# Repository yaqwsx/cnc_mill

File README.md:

# My CNC mill

This repository contains everything related to the
build of my CNC mill. The mill is driven by LinuxCNC.

## Structure

- `arduino_sketches` - I am not a fan of Arduino,
however it is great tool for simple prototypes.
All source codes for prototypes is here.

- `config` - LinuxCNC configuration and HAL files for
the mill

- `hal_modules` - LinuxCNC HAL modules for my custom
hardware

- `hw_modules` - PCBs & firmware for custom hardware

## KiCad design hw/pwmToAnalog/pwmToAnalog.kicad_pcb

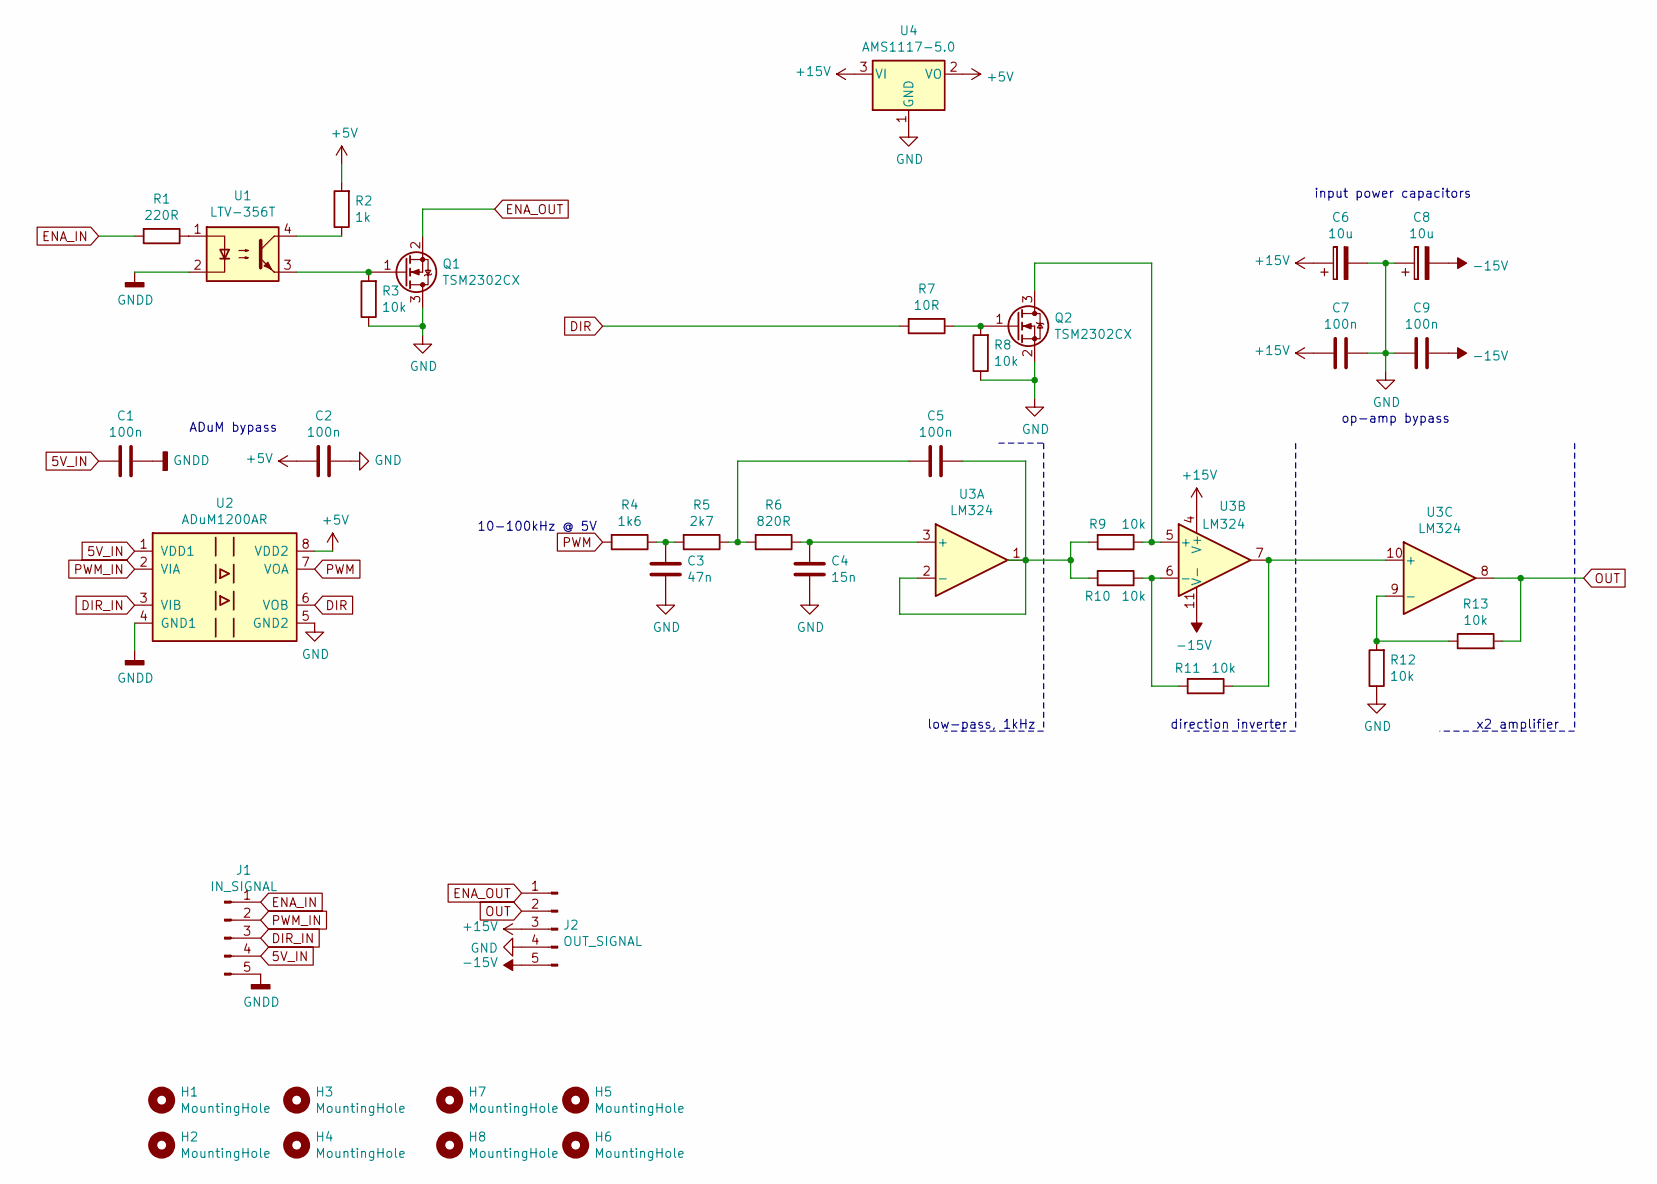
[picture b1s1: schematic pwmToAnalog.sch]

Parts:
C1, C2, C5, C7, C9: 100n; C_0603_1608Metric_Pad1.05x0.95mm_HandSolder
C3: 47n; C_0603_1608Metric_Pad1.05x0.95mm_HandSolder
C4: 15n; C_0603_1608Metric_Pad1.05x0.95mm_HandSolder
C6, C8: 10u; CP_Elec_8x5.4
H1, H2, H3, H4, H5, H6, H7, H8: MountingHole; MountingHole_3.2mm_M3
J1: IN_SIGNAL; TerminalBlock_Phoenix_MKDS-1,5-5_1x05_P5.00mm_Horizontal
J2: OUT_SIGNAL; TerminalBlock_Phoenix_MKDS-1,5-5_1x05_P5.00mm_Horizontal
Q1, Q2: TSM2302CX; SOT-23
R1: 220R; R_0603_1608Metric_Pad1.05x0.95mm_HandSolder
R2: 1k; R_0603_1608Metric_Pad1.05x0.95mm_HandSolder
R3, R8, R9, R10, R11, R12, R13: 10k; R_0603_1608Metric_Pad1.05x0.95mm_HandSolder
R4: 1k6; R_0603_1608Metric_Pad1.05x0.95mm_HandSolder
R5: 2k7; R_0603_1608Metric_Pad1.05x0.95mm_HandSolder
R6: 820R; R_0603_1608Metric_Pad1.05x0.95mm_HandSolder
R7: 10R; R_0603_1608Metric_Pad1.05x0.95mm_HandSolder
U1: LTV-356T; SO-4_4.4x3.6mm_P2.54mm
U2: ADuM1200AR; SOIC-8_3.9x4.9mm_P1.27mm
U3: LM324; SOIC-14_3.9x8.7mm_P1.27mm
U4: AMS1117-5.0; SOT-223-3_TabPin2

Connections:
5V_IN: C1.2, J1.4, U2.1 (VDD1)
+5V: C2.2, R2.2, U2.8 (VDD2), U4.2 (VO)
+15V: C6.1, C7.1, J2.3, U3.4 (V+), U4.3 (VI)
-15V: C8.2, C9.2, J2.5, U3.11 (V-)
DIR: R7.2, U2.6 (VOB)
DIR_IN: J1.3, U2.3 (VIB)
ENA_IN: J1.1, R1.2
ENA_OUT: J2.1, Q1.2 (S)
GND: C2.1, C3.2, C4.2, C6.2, C7.2, C8.1, C9.1, J2.4, Q1.3 (D), Q2.2 (S), R3.1, R8.1, R12.1, U2.5 (GND2), U4.1 (GND)
GNDD: C1.1, J1.5, U1.2, U2.4 (GND1)
unnamed: C3.1, R4.1, R5.2
unnamed: C4.1, R6.1, U3.3 (+)
unnamed: C5.1, R9.2, R10.2, U3.1, U3.2 (-)
unnamed: C5.2, R5.1, R6.2
unnamed: Q1.1 (G), R3.2, U1.3
unnamed: Q2.1 (G), R7.1, R8.2
unnamed: Q2.3 (D), R9.1, U3.5 (+)
unnamed: R1.1, U1.1
unnamed: R2.1, U1.4
unnamed: R10.1, R11.2, U3.6 (-)
unnamed: R11.1, U3.7, U3.10 (+)
unnamed: R12.2, R13.1, U3.9 (-)
OUT: J2.2, R13.2, U3.8
PWM: R4.2, U2.7 (VOA)
PWM_IN: J1.2, U2.2 (VIA)

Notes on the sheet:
low-pass, 1kHz
direction inverter
x2 amplifier
ADuM bypass
op-amp bypass
input power capacitors
10-100kHz @ 5V

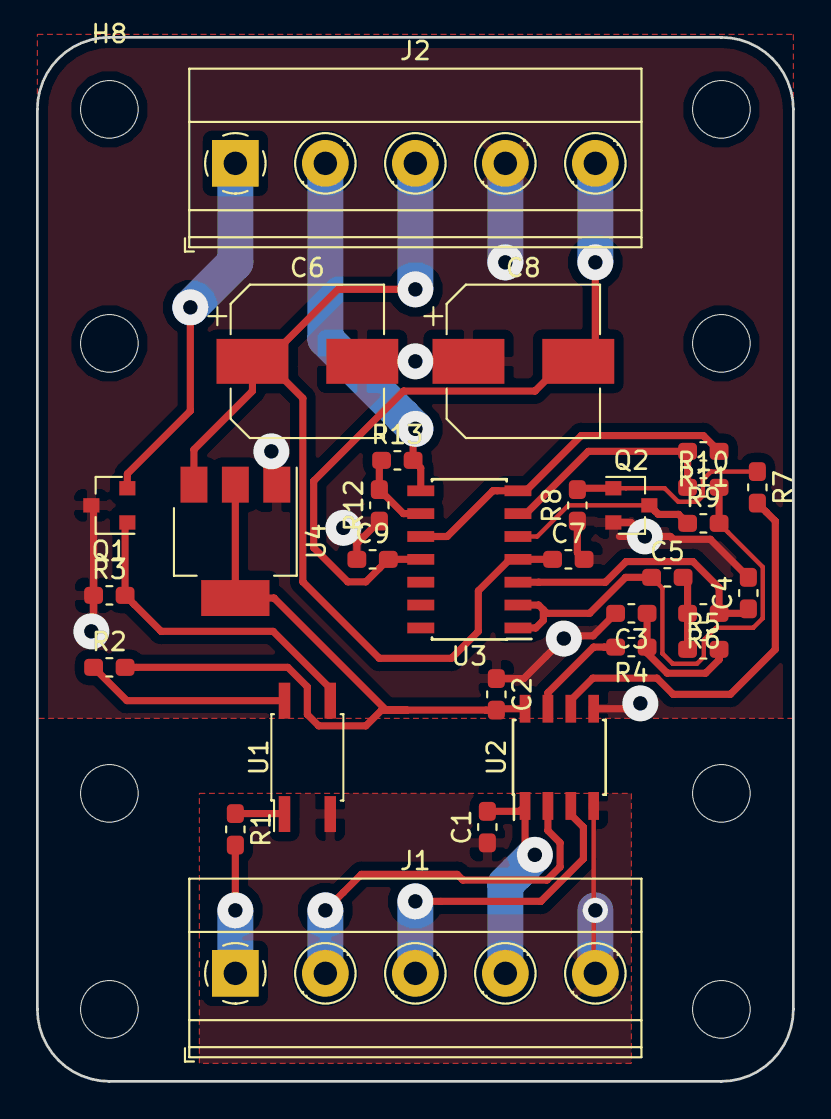
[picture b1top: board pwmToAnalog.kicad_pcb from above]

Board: 2 copper layers, 42.0 x 58.0 mm, 38 parts (0 on the bottom side), 25 nets.

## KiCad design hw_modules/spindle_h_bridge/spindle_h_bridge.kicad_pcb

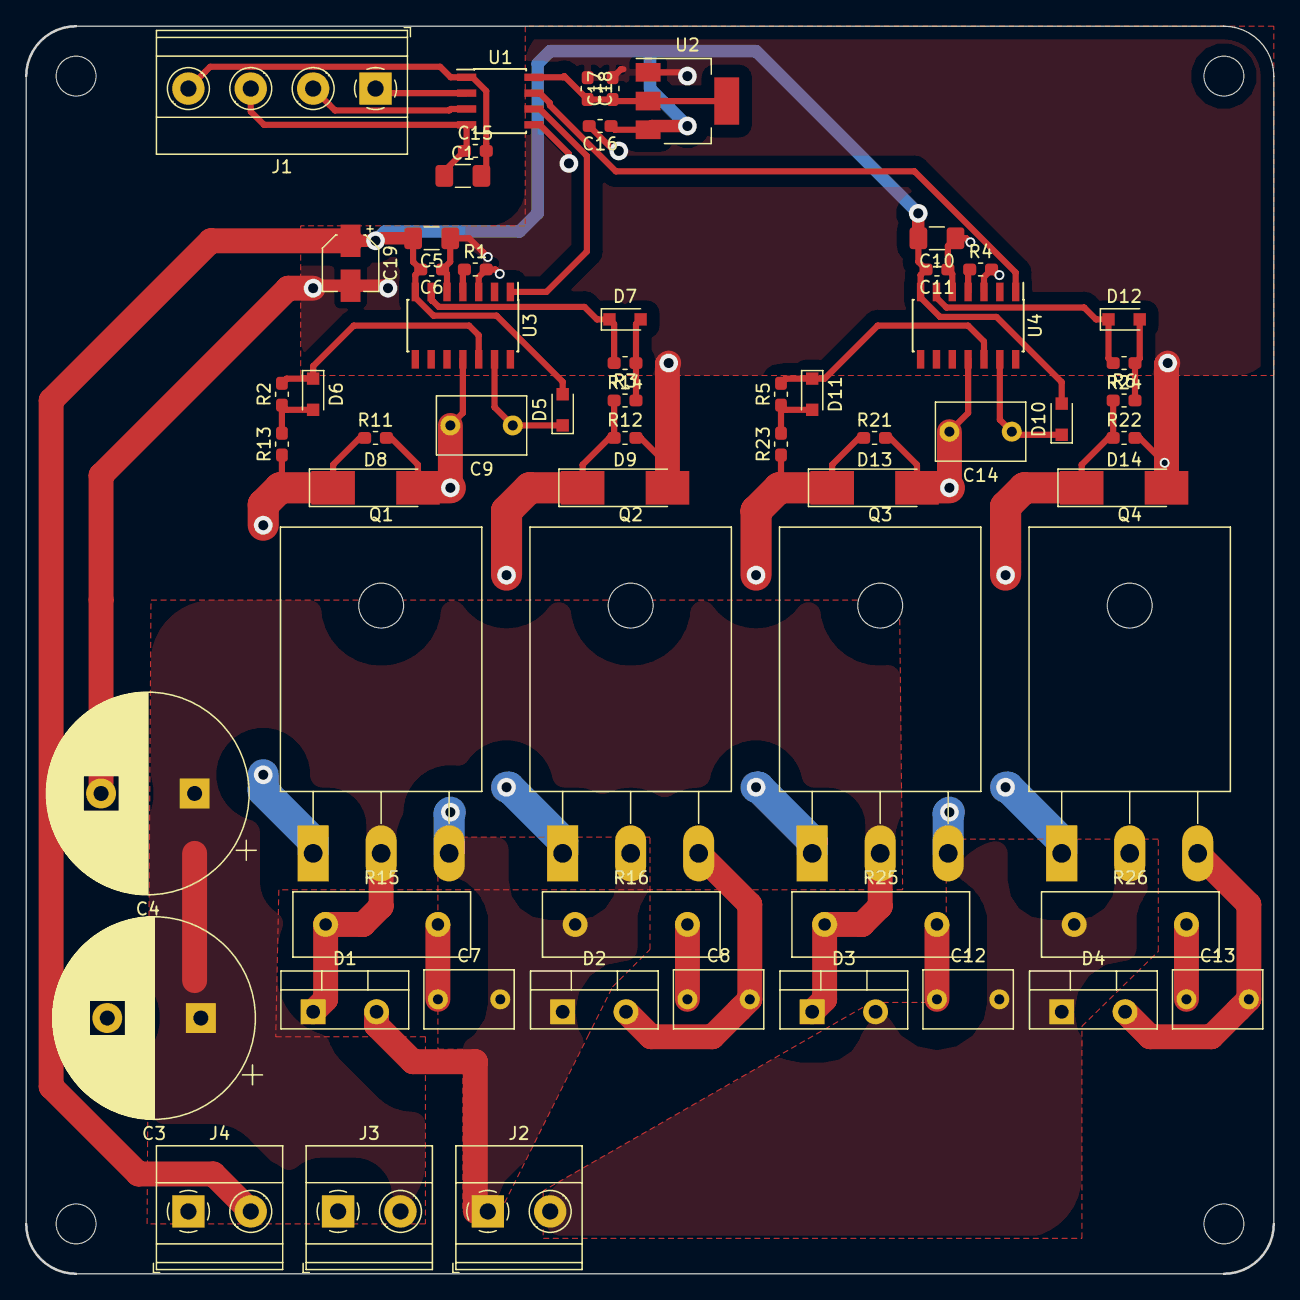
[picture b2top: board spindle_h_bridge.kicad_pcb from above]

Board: 4 copper layers, 100.0 x 100.0 mm, 66 parts (0 on the bottom side), 32 nets.

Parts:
C1: 2u2; C_1206_3216Metric_Pad1.42x1.75mm_HandSolder
C3: 220u 400V; CP_Radial_D16.0mm_P7.50mm
C4: 10u 400V; CP_Radial_D16.0mm_P7.50mm
C5, C10: 1u; C_1206_3216Metric_Pad1.42x1.75mm_HandSolder
C6, C11, C15, C16, C18: 100n; C_0603_1608Metric_Pad1.05x0.95mm_HandSolder
C7, C8, C9, C12, C13, C14: 100n 400V; C_Rect_L7.0mm_W4.5mm_P5.00mm
C17: 10u; C_0603_1608Metric_Pad1.05x0.95mm_HandSolder
C19: 10u; CP_Elec_4x4.5
D1, D2, D3, D4: STTH15R06; TO-220-2_Vertical
D5, D6, D7, D10, D11, D12: BAT42; D_SOD-323_HandSoldering
D8, D9, D13, D14: 18V; D_MELF_Handsoldering
H1, H2, H3, H4: MountingHole; MountingHole_3.2mm_M3
J1: SIGNAL; TerminalBlock_Phoenix_MKDS-1,5-4_1x04_P5.00mm_Horizontal
J2: MOTOR; TerminalBlock_Phoenix_MKDS-1,5-2_1x02_P5.00mm_Horizontal
J3, J4: POWER; TerminalBlock_Phoenix_MKDS-1,5-2_1x02_P5.00mm_Horizontal
Q1, Q2, Q3, Q4: IRG4PH40U; TO-247-3_Horizontal_TabDown
R1, R4: 25k; R_0603_1608Metric_Pad1.05x0.95mm_HandSolder
R2, R3, R5, R6: 10R; R_0603_1608Metric_Pad1.05x0.95mm_HandSolder
R11, R12, R21, R22: 10k; R_0603_1608Metric_Pad1.05x0.95mm_HandSolder
R13, R14, R23, R24: 4R7; R_0603_1608Metric_Pad1.05x0.95mm_HandSolder
R15, R16, R25, R26: 0R5; R_Box_L14.0mm_W5.0mm_P9.00mm
U1: ADuM1200AR; SOIC-8_3.9x4.9mm_P1.27mm
U2: LM1117-5.0; SOT-223
U3, U4: FAN7393A; SOIC-14_3.9x8.7mm_P1.27mm

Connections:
+5V: C1.2, C15.2, J1.4, U1.1
+15V: C5.2, C6.2, C10.2, C11.2, C16.1, C19.1, D5.2, D10.2, J4.2, U2.3, U3.7, U4.7
/left-half-bridge/OUT: C7.2, C9.2, D1.2, D2.1, D8.2, J2.1, Q1.3, Q2.2, R11.2, R16.1, U3.11
/left-half-bridge/PWM: U1.6, U3.1
/right-half-bridge/OUT: C12.2, C14.2, D3.2, D4.1, D13.2, J2.2, Q3.3, Q4.2, R21.2, R26.1, U4.11
/right-half-bridge/PWM: U1.7, U4.1
A: J1.1, U1.2
B: J1.2, U1.3
GND: C3.2, C4.2, C5.1, C6.1, C8.2, C10.1, C11.1, C13.2, C16.2, C17.2, C18.1, C19.2, D2.2, D4.2, D9.2, D14.2, J3.1, J4.1, Q2.3, Q4.3, R1.2, R4.2, R12.2, R22.2, U1.5, U2.1, U3.3, U3.5, U4.3, U4.5
GNDD: C1.1, C15.1, J1.3, U1.4
unnamed: C7.1, R15.2
unnamed: C8.1, R16.2
unnamed: C9.1, D5.1, U3.13
unnamed: C12.1, R25.2
unnamed: C13.1, R26.2
unnamed: C14.1, D10.1, U4.13
unnamed: C17.1, C18.2, U1.8, U2.2, U2.4
unnamed: D6.1, R2.2, U3.12
unnamed: D6.2, R2.1, R13.2
unnamed: D7.1, R3.2, U3.6
unnamed: D7.2, R3.1, R14.2
unnamed: D8.1, Q1.1, R11.1, R13.1
unnamed: D9.1, Q2.1, R12.1, R14.1
unnamed: D11.1, R5.2, U4.12
unnamed: D11.2, R5.1, R23.2
unnamed: D12.1, R6.2, U4.6
unnamed: D12.2, R6.1, R24.2
unnamed: D13.1, Q3.1, R21.1, R23.1
unnamed: D14.1, Q4.1, R22.1, R24.1
unnamed: R1.1, U3.4
unnamed: R4.1, U4.4
VCC: C3.1, C4.1, D1.1, D3.1, J3.2, Q1.2, Q3.2, R15.1, R25.1

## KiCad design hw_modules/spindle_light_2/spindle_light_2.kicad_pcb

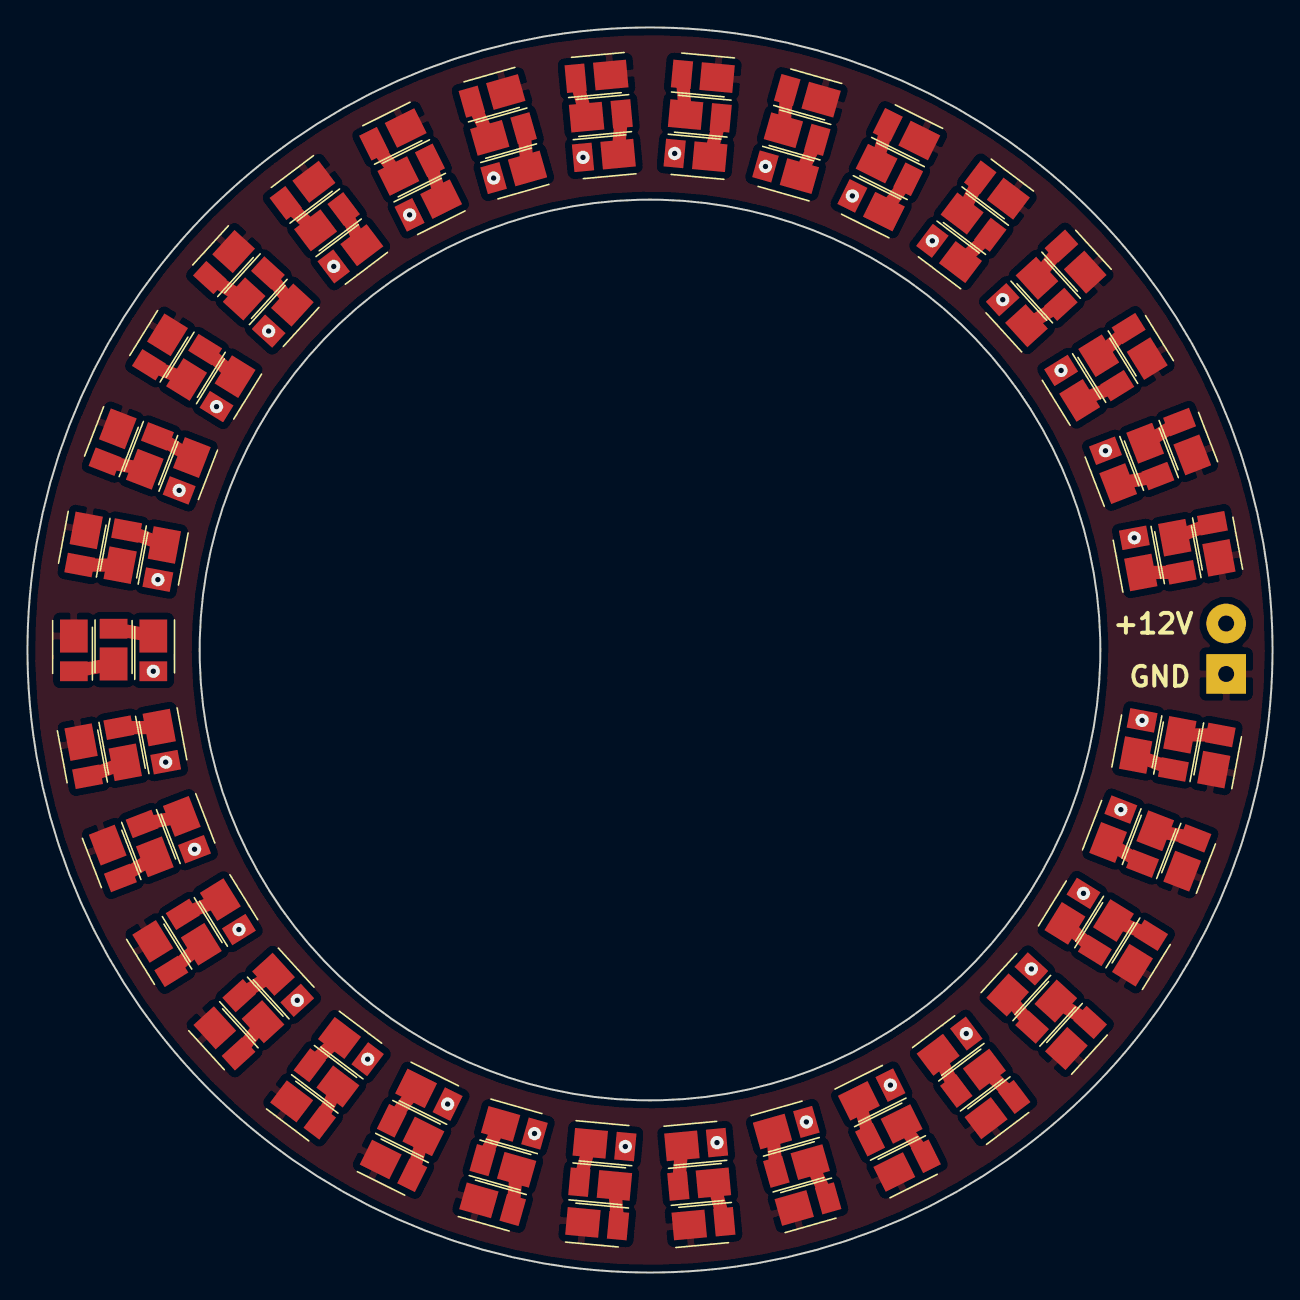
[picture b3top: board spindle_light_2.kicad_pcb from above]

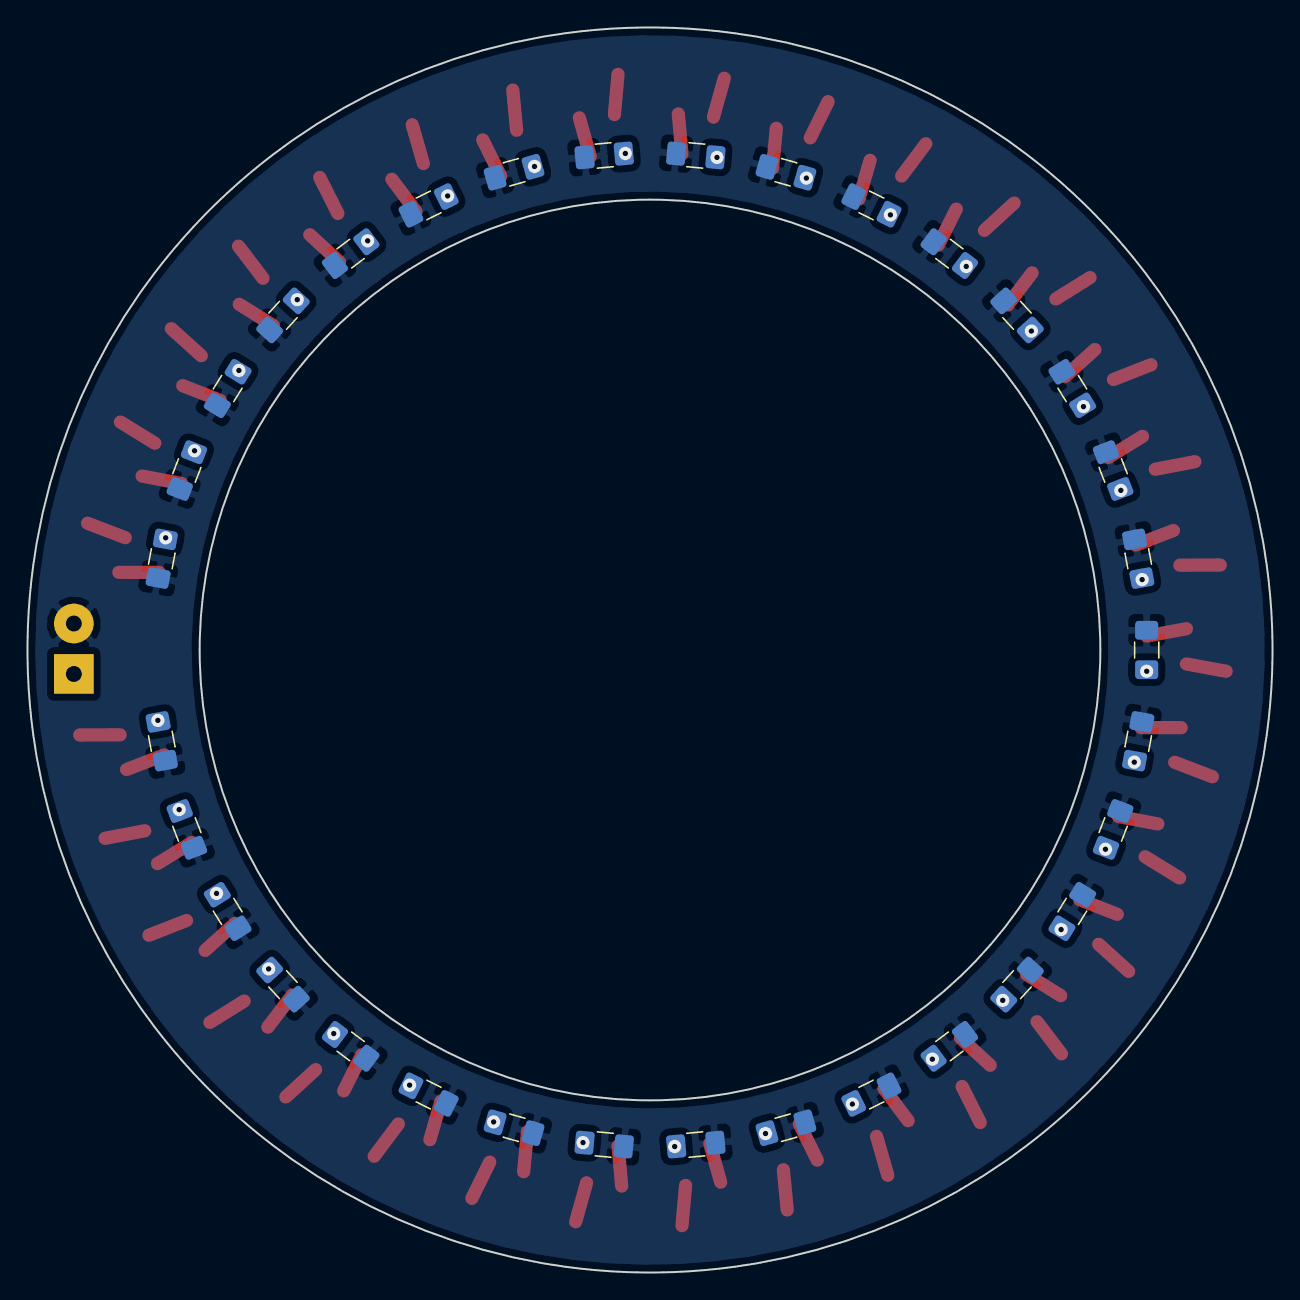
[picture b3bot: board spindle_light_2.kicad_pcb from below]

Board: 2 copper layers, 94.0 x 94.0 mm, 133 parts (33 on the bottom side), 101 nets.

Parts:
D1, D2, D3, D4, D5, D6, D7, D8, D9, D10, D11, D12, D13, D14, D15, D16, D17, D18, D19, D20, D21, D22, D23, D24, D25, D26, D27, D28, D29, D30, D31, D32, D33, D34, D35, D36, D37, D38, D39, D40, D41, D42, D43, D44, D45, D46, D47, D48, D49, D50, D51, D52, D53, D54, D55, D56, D57, D58, D59, D60, D61, D62, D63, D64, D65, D66, D67, D68, D69, D70, D71, D72, D73, D74, D75, D76, D77, D78, D79, D80, D81, D82, D83, D84, D85, D86, D87, D88, D89, D90, D91, D92, D93, D94, D95, D96, D97, D98, D99: LED; LED_PLCC_2835_Handsoldering_Centered
J1: Power; SolderWirePad_1x02_P3.81mm_Drill1.2mm
R1, R2, R3, R4, R5, R6, R7, R8, R9, R10, R11, R12, R13, R14, R15, R16, R17, R18, R19, R20, R21, R22, R23, R24, R25, R26, R27, R28, R29, R30, R31, R32, R33: 47R; R_1206_3216Metric_Pad1.42x1.75mm_HandSolder

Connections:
+12V: J1.2, R1.1, R2.1, R3.1, R4.1, R5.1, R6.1, R7.1, R8.1, R9.1, R10.1, R11.1, R12.1, R13.1, R14.1, R15.1, R16.1, R17.1, R18.1, R19.1, R20.1, R21.1, R22.1, R23.1, R24.1, R25.1, R26.1, R27.1, R28.1, R29.1, R30.1, R31.1, R32.1, R33.1
GND: D3.1, D6.1, D9.1, D12.1, D15.1, D18.1, D21.1, D24.1, D27.1, D30.1, D33.1, D36.1, D39.1, D42.1, D45.1, D48.1, D51.1, D54.1, D57.1, D60.1, D63.1, D66.1, D69.1, D72.1, D75.1, D78.1, D81.1, D84.1, D87.1, D90.1, D93.1, D96.1, D99.1, J1.1
unnamed: D1.1, D2.2
unnamed: D1.2, R1.2
unnamed: D2.1, D3.2
unnamed: D4.1, D5.2
unnamed: D4.2, R2.2
unnamed: D5.1, D6.2
unnamed: D7.1, D8.2
unnamed: D7.2, R3.2
unnamed: D8.1, D9.2
unnamed: D10.1, D11.2
unnamed: D10.2, R4.2
unnamed: D11.1, D12.2
unnamed: D13.1, D14.2
unnamed: D13.2, R5.2
unnamed: D14.1, D15.2
unnamed: D16.1, D17.2
unnamed: D16.2, R6.2
unnamed: D17.1, D18.2
unnamed: D19.1, D20.2
unnamed: D19.2, R7.2
unnamed: D20.1, D21.2
unnamed: D22.1, D23.2
unnamed: D22.2, R8.2
unnamed: D23.1, D24.2
unnamed: D25.1, D26.2
unnamed: D25.2, R9.2
unnamed: D26.1, D27.2
unnamed: D28.1, D29.2
unnamed: D28.2, R10.2
unnamed: D29.1, D30.2
unnamed: D31.1, D32.2
unnamed: D31.2, R11.2
unnamed: D32.1, D33.2
unnamed: D34.1, D35.2
unnamed: D34.2, R12.2
unnamed: D35.1, D36.2
unnamed: D37.1, D38.2
unnamed: D37.2, R13.2
unnamed: D38.1, D39.2
unnamed: D40.1, D41.2
unnamed: D40.2, R14.2
unnamed: D41.1, D42.2
unnamed: D43.1, D44.2
unnamed: D43.2, R15.2
unnamed: D44.1, D45.2
unnamed: D46.1, D47.2
unnamed: D46.2, R16.2
unnamed: D47.1, D48.2
unnamed: D49.1, D50.2
unnamed: D49.2, R17.2
unnamed: D50.1, D51.2
unnamed: D52.1, D53.2
unnamed: D52.2, R18.2
unnamed: D53.1, D54.2
unnamed: D55.1, D56.2
unnamed: D55.2, R19.2
unnamed: D56.1, D57.2
unnamed: D58.1, D59.2
unnamed: D58.2, R20.2
unnamed: D59.1, D60.2
unnamed: D61.1, D62.2
unnamed: D61.2, R21.2
unnamed: D62.1, D63.2
unnamed: D64.1, D65.2
unnamed: D64.2, R22.2
unnamed: D65.1, D66.2
unnamed: D67.1, D68.2
unnamed: D67.2, R23.2
unnamed: D68.1, D69.2
unnamed: D70.1, D71.2
unnamed: D70.2, R24.2
unnamed: D71.1, D72.2
unnamed: D73.1, D74.2
unnamed: D73.2, R25.2
unnamed: D74.1, D75.2
unnamed: D76.1, D77.2
unnamed: D76.2, R26.2
unnamed: D77.1, D78.2
unnamed: D79.1, D80.2
unnamed: D79.2, R27.2
unnamed: D80.1, D81.2
unnamed: D82.1, D83.2
unnamed: D82.2, R28.2
unnamed: D83.1, D84.2
unnamed: D85.1, D86.2
unnamed: D85.2, R29.2
unnamed: D86.1, D87.2
unnamed: D88.1, D89.2
unnamed: D88.2, R30.2
unnamed: D89.1, D90.2
unnamed: D91.1, D92.2
unnamed: D91.2, R31.2
unnamed: D92.1, D93.2
unnamed: D94.1, D95.2
unnamed: D94.2, R32.2
unnamed: D95.1, D96.2
unnamed: D97.1, D98.2
unnamed: D97.2, R33.2
unnamed: D98.1, D99.2

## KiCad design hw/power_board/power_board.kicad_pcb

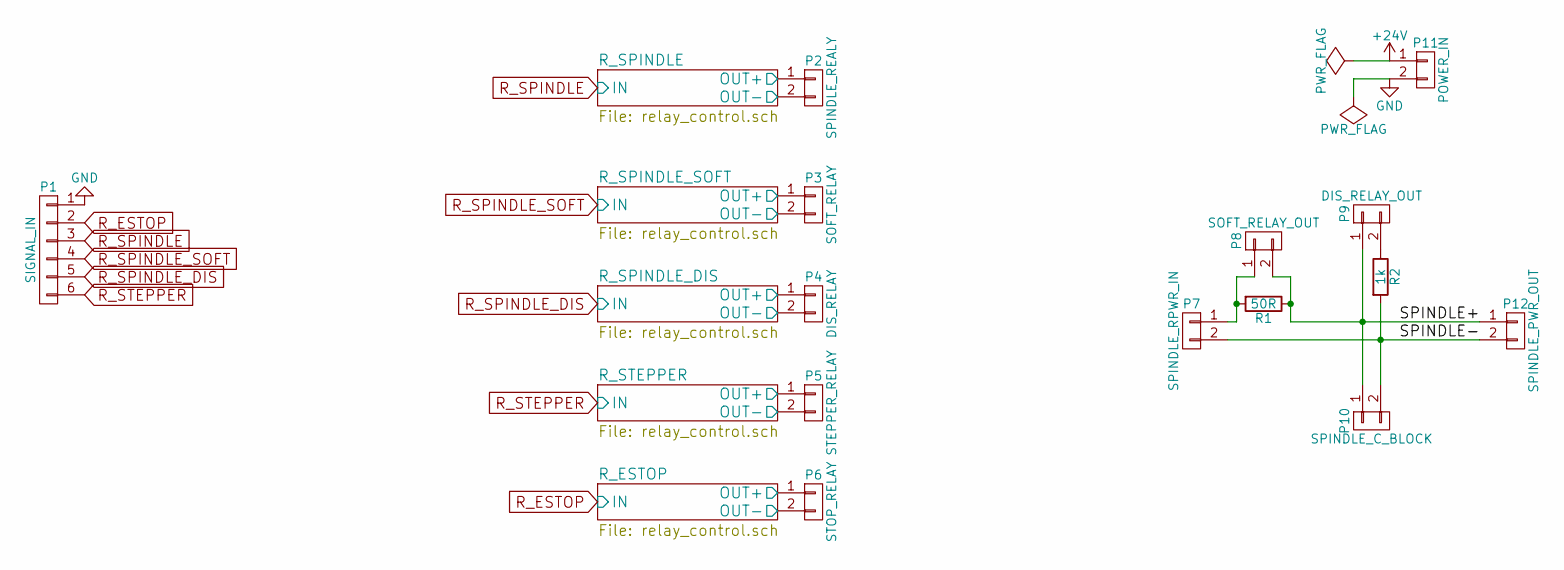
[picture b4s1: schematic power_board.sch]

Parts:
P1: SIGNAL_IN; TerminalBlock_Pheonix_MKDS1.5-6pol
P2: SPINDLE_REALY; TerminalBlock_Pheonix_MKDS1.5-2pol
P3: SOFT_RELAY; TerminalBlock_Pheonix_MKDS1.5-2pol
P4: DIS_RELAY; TerminalBlock_Pheonix_MKDS1.5-2pol
P5: STEPPER_RELAY; TerminalBlock_Pheonix_MKDS1.5-2pol
P6: STOP_RELAY; TerminalBlock_Pheonix_MKDS1.5-2pol
P7: SPINDLE_RPWR_IN; TerminalBlock_Pheonix_MKDS1.5-2pol
P8: SOFT_RELAY_OUT; TerminalBlock_Pheonix_MKDS1.5-2pol
P9: DIS_RELAY_OUT; TerminalBlock_Pheonix_MKDS1.5-2pol
P10: SPINDLE_C_BLOCK; TerminalBlock_Pheonix_MKDS1.5-2pol
P11: POWER_IN; TerminalBlock_Pheonix_MKDS1.5-2pol
P12: SPINDLE_PWR_OUT; TerminalBlock_Pheonix_MKDS1.5-2pol
R1: 50R; Resistor_Horizontal_RM30mm
R2: 1k; Resistor_Horizontal_RM30mm

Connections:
+24V: P2.1, P3.1, P4.1, P5.1, P6.1, P11.1; also elsewhere on the board
/R_ESTOP/OUT-: P6.2; also elsewhere on the board
/R_SPINDLE/OUT-: P2.2; also elsewhere on the board
/R_SPINDLE_DIS/OUT-: P4.2; also elsewhere on the board
/R_SPINDLE_SOFT/OUT-: P3.2; also elsewhere on the board
/R_STEPPER/OUT-: P5.2; also elsewhere on the board
/SPINDLE+: P8.2, P9.1, P10.1, P12.1, R1.1
/SPINDLE-: P7.2, P10.2, P12.2, R2.2
GND: P1.1, P11.2; also elsewhere on the board
unnamed: P7.1, P8.1, R1.2
unnamed: P9.2, R2.1
R_ESTOP: P1.2; also elsewhere on the board
R_SPINDLE: P1.3; also elsewhere on the board
R_SPINDLE_DIS: P1.5; also elsewhere on the board
R_SPINDLE_SOFT: P1.4; also elsewhere on the board
R_STEPPER: P1.6; also elsewhere on the board

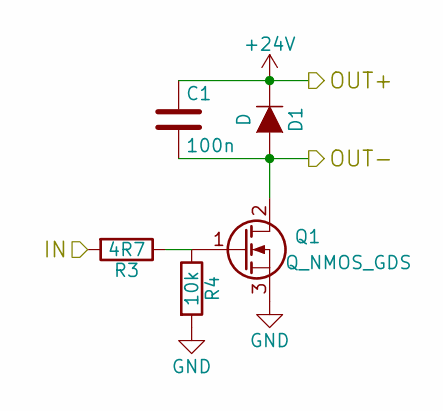
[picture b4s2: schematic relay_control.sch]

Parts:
C1: 100n; C_0603
D1: D; SOD-523
Q1: Q_NMOS_GDS; SOT-223
R3: 4R7; R_0603
R4: 10k; R_0603

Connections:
+24V: C1.1, D1.1 (K); also elsewhere on the board
/R_SPINDLE/OUT-: C1.2, D1.2 (A), Q1.2 (D); also elsewhere on the board
GND: Q1.3 (S), R4.2; also elsewhere on the board
unnamed: Q1.1 (G), R3.1, R4.1
R_SPINDLE: R3.2; also elsewhere on the board

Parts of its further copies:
C2, C3, C4, C5: 100n; C_0603
D2, D3, D4, D5: D; SOD-523
Q2, Q3, Q4, Q5: Q_NMOS_GDS; SOT-223
R5, R7, R9, R11: 4R7; R_0603
R6, R8, R10, R12: 10k; R_0603

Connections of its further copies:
+24V: C2.1, C3.1, C4.1, C5.1, D2.1 (K), D3.1 (K), D4.1 (K), D5.1 (K); also elsewhere on the board
/R_ESTOP/OUT-: C5.2, D5.2 (A), Q5.2 (D); also elsewhere on the board
/R_SPINDLE_DIS/OUT-: C3.2, D3.2 (A), Q3.2 (D); also elsewhere on the board
/R_SPINDLE_SOFT/OUT-: C2.2, D2.2 (A), Q2.2 (D); also elsewhere on the board
/R_STEPPER/OUT-: C4.2, D4.2 (A), Q4.2 (D); also elsewhere on the board
GND: Q2.3 (S), Q3.3 (S), Q4.3 (S), Q5.3 (S), R6.2, R8.2, R10.2, R12.2; also elsewhere on the board
unnamed: Q2.1 (G), R5.1, R6.1
unnamed: Q3.1 (G), R7.1, R8.1
unnamed: Q4.1 (G), R9.1, R10.1
unnamed: Q5.1 (G), R11.1, R12.1
R_ESTOP: R11.2; also elsewhere on the board
R_SPINDLE_DIS: R7.2; also elsewhere on the board
R_SPINDLE_SOFT: R5.2; also elsewhere on the board
R_STEPPER: R9.2; also elsewhere on the board

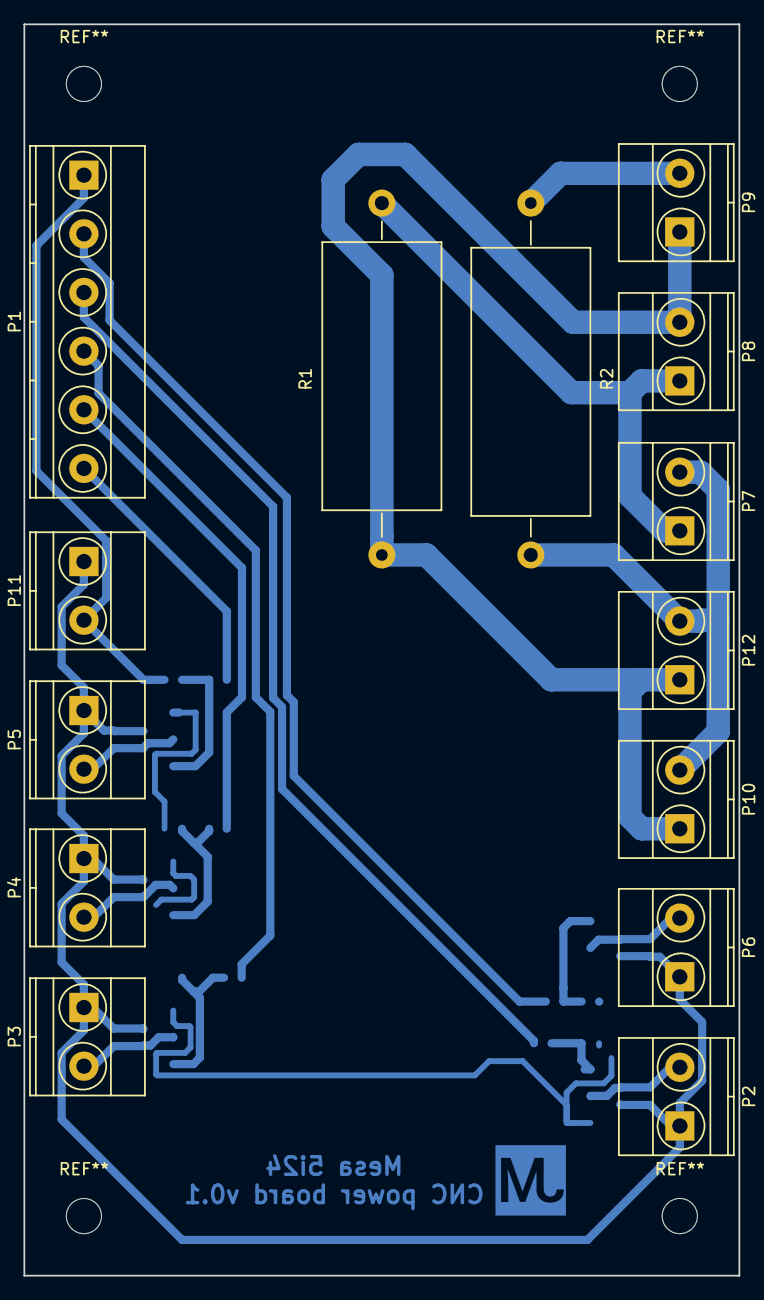
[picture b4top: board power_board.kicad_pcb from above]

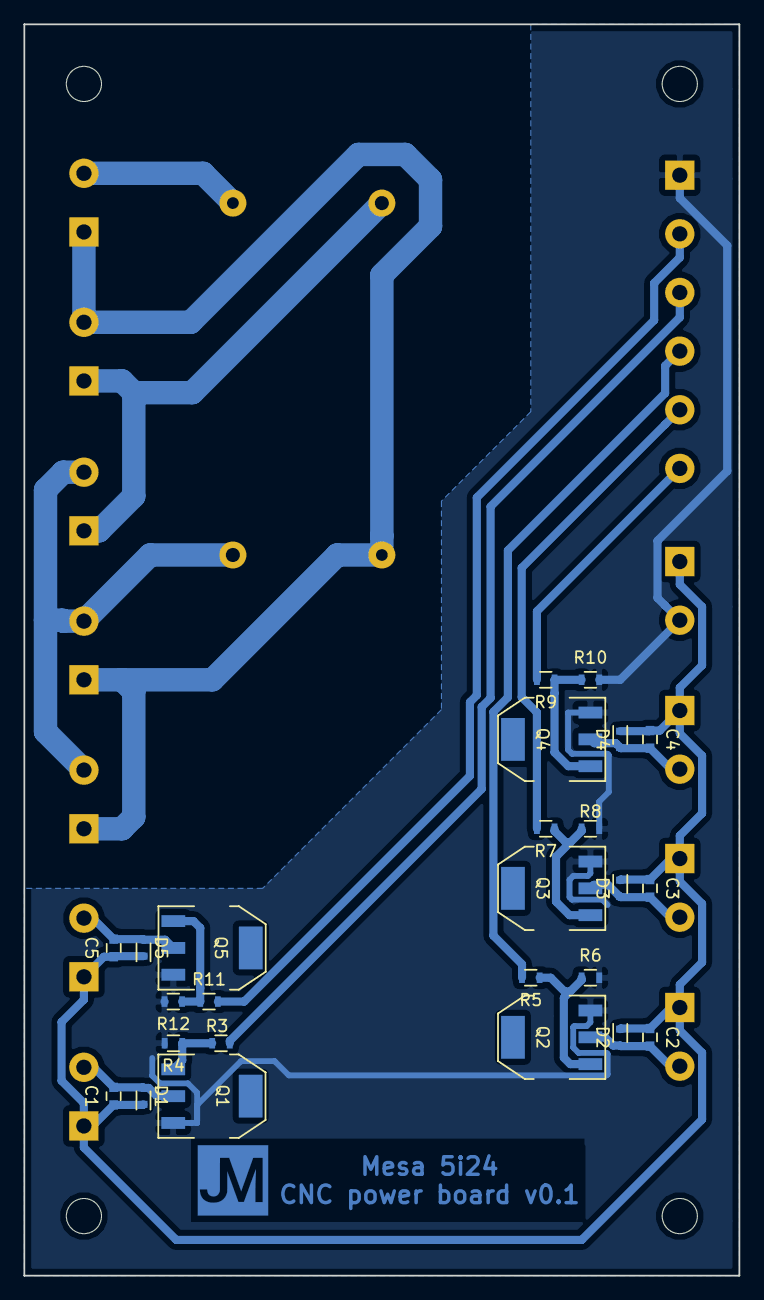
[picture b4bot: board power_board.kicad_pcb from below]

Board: 2 copper layers, 61.0 x 106.7 mm, 39 parts (25 on the bottom side), 21 nets.

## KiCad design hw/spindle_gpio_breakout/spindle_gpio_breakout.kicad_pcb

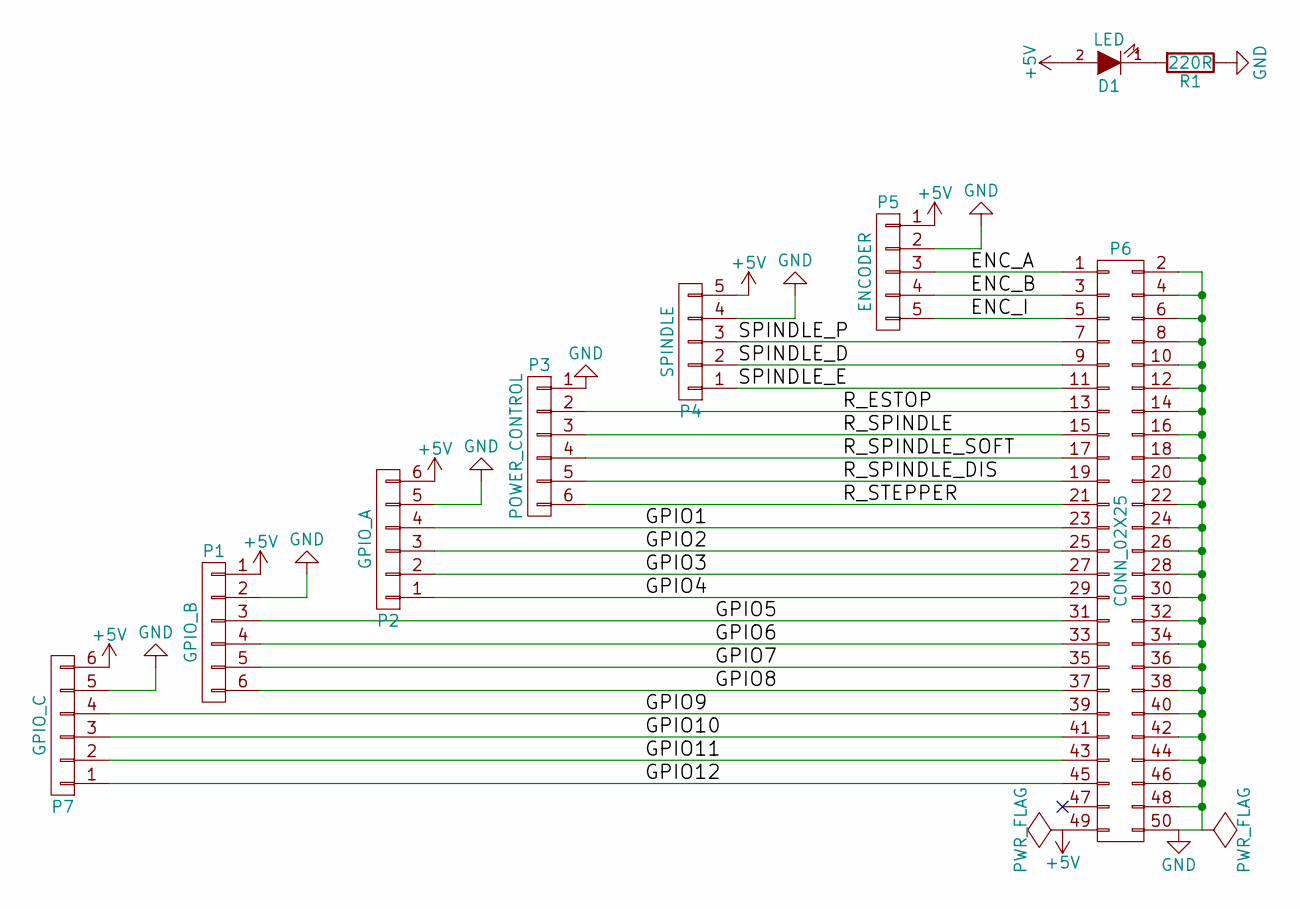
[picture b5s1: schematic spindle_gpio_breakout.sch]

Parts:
D1: LED; LED_1206
P1: GPIO_B; TerminalBlock_Pheonix_MKDS1.5-6pol
P2: GPIO_A; TerminalBlock_Pheonix_MKDS1.5-6pol
P3: POWER_CONTROL; TerminalBlock_Pheonix_MKDS1.5-6pol
P4: SPINDLE; TerminalBlock_Pheonix_MKDS1.5-5pol
P5: ENCODER; TerminalBlock_Pheonix_MKDS1.5-5pol
P6: CONN_02X25; IDC_Header_Straight_50pins
P7: GPIO_C; TerminalBlock_Pheonix_MKDS1.5-6pol
R1: 220R; R_0603

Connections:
+5V: D1.2 (A), P1.1, P2.6, P4.5, P5.1, P6.49, P7.6
/ENC_A: P5.3, P6.1
/ENC_B: P5.4, P6.3
/ENC_I: P5.5, P6.5
/GPIO1: P2.4, P6.23
/GPIO2: P2.3, P6.25
/GPIO3: P2.2, P6.27
/GPIO4: P2.1, P6.29
/GPIO5: P1.3, P6.31
/GPIO6: P1.4, P6.33
/GPIO7: P1.5, P6.35
/GPIO8: P1.6, P6.37
/GPIO9: P6.39, P7.4
/GPIO10: P6.41, P7.3
/GPIO11: P6.43, P7.2
/GPIO12: P6.45, P7.1
/R_ESTOP: P3.2, P6.13
/R_SPINDLE: P3.3, P6.15
/R_SPINDLE_DIS: P3.5, P6.19
/R_SPINDLE_SOFT: P3.4, P6.17
/R_STEPPER: P3.6, P6.21
/SPINDLE_D: P4.2, P6.9
/SPINDLE_E: P4.1, P6.11
/SPINDLE_P: P4.3, P6.7
GND: P1.2, P2.5, P3.1, P4.4, P5.2, P6.2, P6.4, P6.6, P6.8, P6.10, P6.12, P6.14, P6.16, P6.18, P6.20, P6.22, P6.24, P6.26, P6.28, P6.30, P6.32, P6.34, P6.36, P6.38, P6.40, P6.42, P6.44, P6.46, P6.48, P6.50, P7.5, R1.1
unnamed: D1.1 (K), R1.2

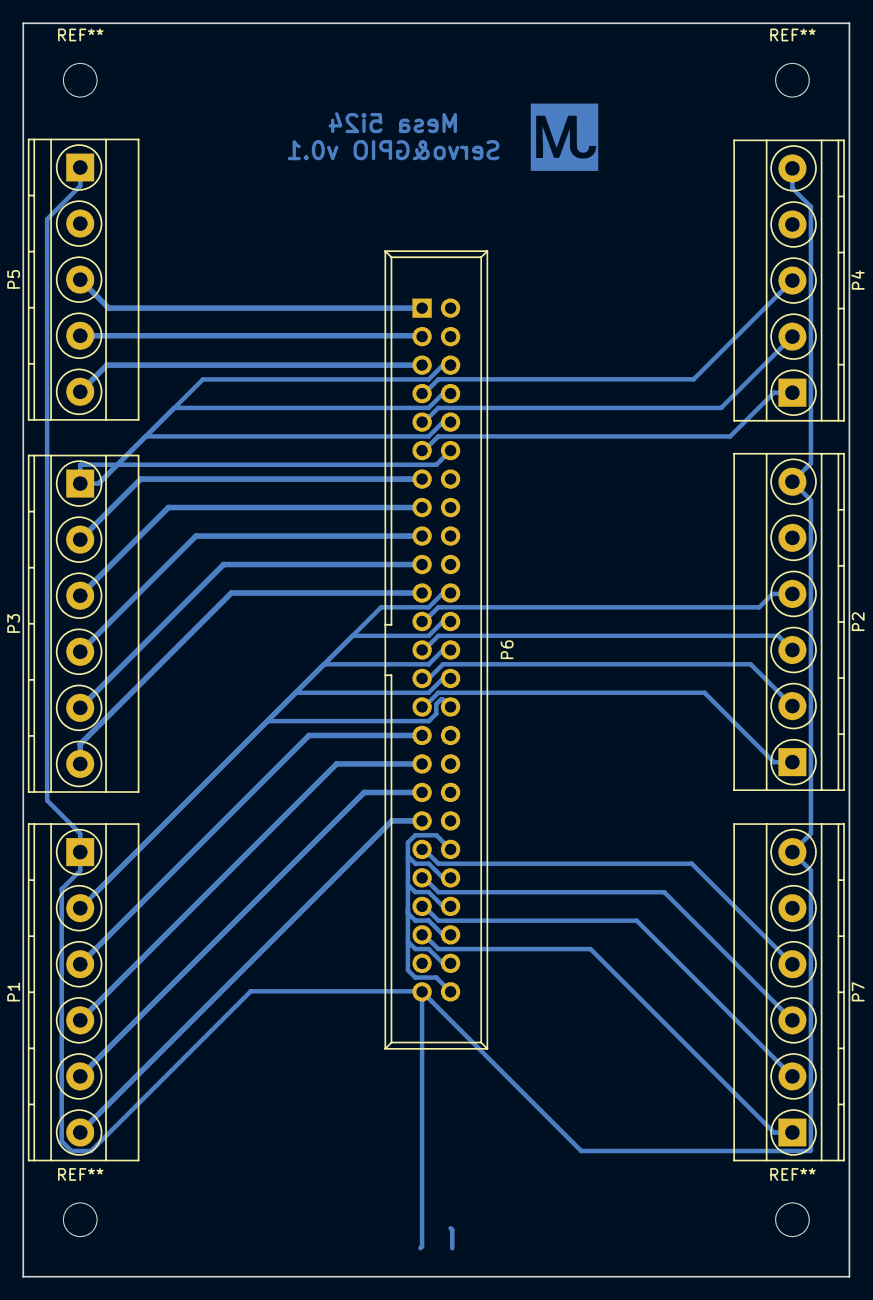
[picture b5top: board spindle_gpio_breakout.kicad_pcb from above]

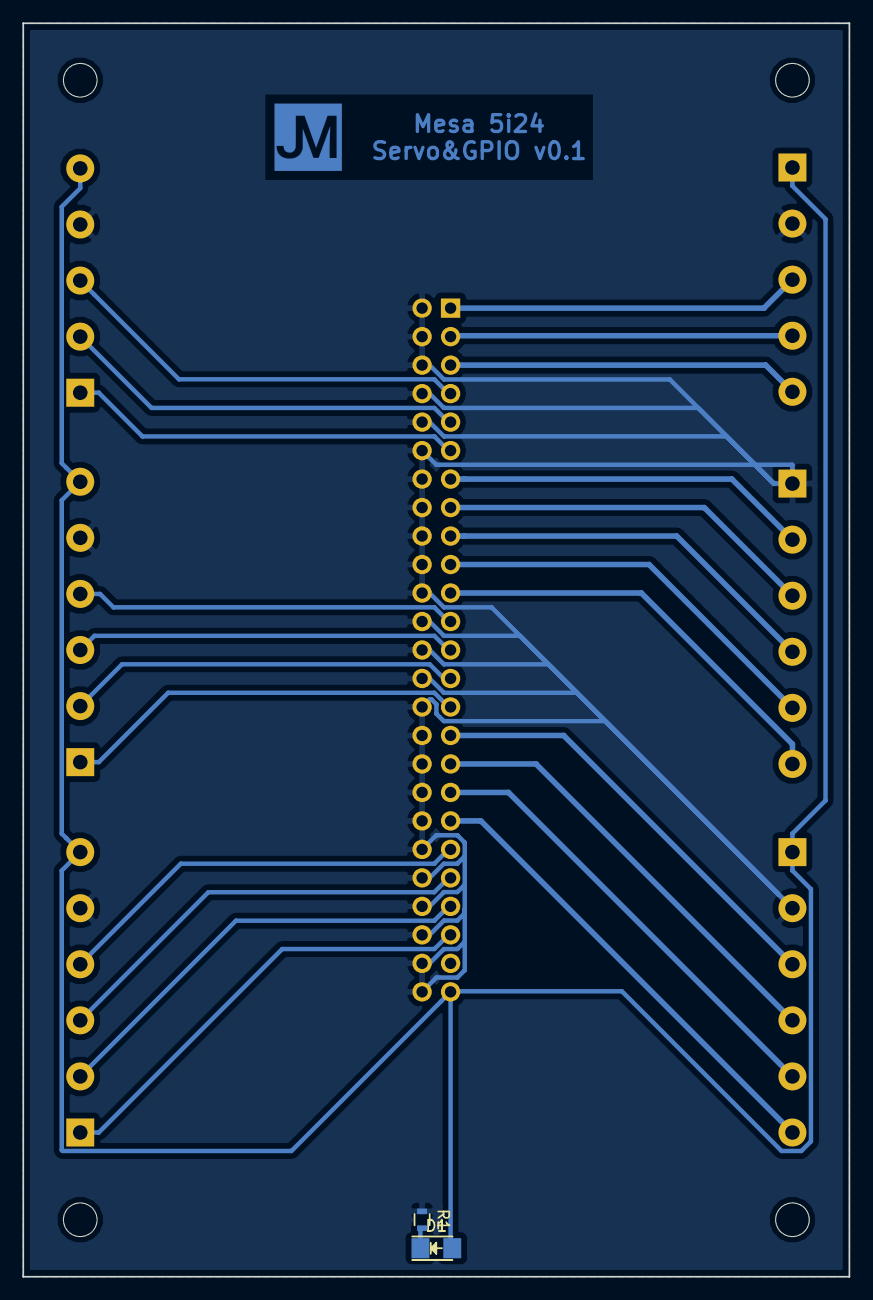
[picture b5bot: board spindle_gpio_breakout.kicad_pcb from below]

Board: 2 copper layers, 73.7 x 111.8 mm, 9 parts (2 on the bottom side), 26 nets.
